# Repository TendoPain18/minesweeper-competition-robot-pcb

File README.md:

# Minesweeper Competition Robot — PCB Design 🤖💣

Custom KiCad-designed PCBs for a minesweeper competition robot, consisting of a **Control PCB** housing the main microcontroller and sensing/driving circuitry, and a **Power PCB** acting as a smart relay system for safely switching robot subsystems on and off.

<div align="center">
  
</div>

<br>
<div align="center">
  
</div>

## 📋 About

Both PCBs were fully designed from schematic to layout in **KiCad** and manufactured as real printed circuit boards. The two boards work together: the Control PCB handles all logic, motor driving, sensing, and protection, while the Power PCB receives switching commands from the Control PCB and safely controls power delivery to the robot's subsystems.

## 🛠️ Tools Used

- **KiCad** — Schematic capture and PCB layout
- **Arduino IDE** — Firmware for the Arduino Mega

---

## 🟦 Control PCB

The brain of the robot. Hosts the microcontroller and all peripheral circuitry needed to drive motors, read sensors, and manage safe shutdown.

<div align="center">
  
</div>

<div align="center">
  
</div>

### Key Components

- **Arduino Mega** — Main microcontroller
- **Two HW-315 Motor Driver Modules** — Drive the main locomotion motors
- **H-Bridge** — Additional motor driving stage
- **Two MPU-6050 IMUs** — Inertial measurement units for orientation sensing
- **Auto Safe-Shutdown Circuit** — Capacitor-backed circuit using ICs, capacitors, and resistors that detects power loss and safely closes the system before supply rails collapse

### Connector Pins / Interfaces

| Interface | Description |
|-----------|-------------|
| Motor Control ×2 | PWM/direction signals for drive motors |
| Motor Driver ×2 | Power outputs to HW-315 modules |
| Encoder ×2 | Quadrature encoder inputs for wheel odometry |
| Arm Motor | Control signal for the mine-detection arm |
| 9V Battery | Main power input |
| Power PCB Link | Control signals sent to the Power PCB |

### PCB Photos

<div align="center">
  
</div>

<div align="center">

</div>

### Safe Shutdown Circuit

A key protection feature of the Control PCB is the automatic safe-shutdown circuit. When the power supply is cut or drops below a safe threshold, the capacitor bank holds enough energy to allow the ICs to complete a controlled shutdown sequence, preventing state corruption and protecting the motor drivers from abrupt power loss.

---

## 🟥 Power PCB

Acts as a smart relay board, receiving switching signals from the Control PCB and toggling power to the robot's subsystems in a safe, controlled manner.

<div align="center">
  
</div>

<div align="center">
  
</div>

### Key Features

- Receives control signals from the Control PCB
- Safely switches power to robot subsystems on and off
- Protects against back-EMF and switching transients
- Designed for low-resistance power paths to minimise losses

### PCB Photos

<div align="center">
  
</div>

<div align="center">

</div>

---

## 🖨️ Manufactured Boards

<div align="center">
  
</div>

*Fully assembled and populated PCBs ready for robot integration*

---

## 📄 License

This project is licensed under the MIT License - see the [LICENSE](LICENSE) file for details.

## 🙏 Acknowledgments

- KiCad open-source EDA tool
- Competition organizers for the design challenge

## <!-- CONTACT -->
<div id="toc" align="center">
  <ul style="list-style: none">
    <summary>
      <h2 align="center">
        🚀
        CONTACT ME
        🚀
      </h2>
    </summary>
  </ul>
</div>
<table align="center" style="width: 100%; max-width: 600px;">
<tr>
  <td style="width: 20%; text-align: center;">
    
  </td>
  <td style="width: 20%; text-align: center;">
    
  </td>
  <td style="width: 20%; text-align: center;">
    
  </td>
  <td style="width: 20%; text-align: center;">
    
  </td>
  <td style="width: 20%; text-align: center;">
    
  </td>
</tr>
</table>
<!-- END CONTACT -->

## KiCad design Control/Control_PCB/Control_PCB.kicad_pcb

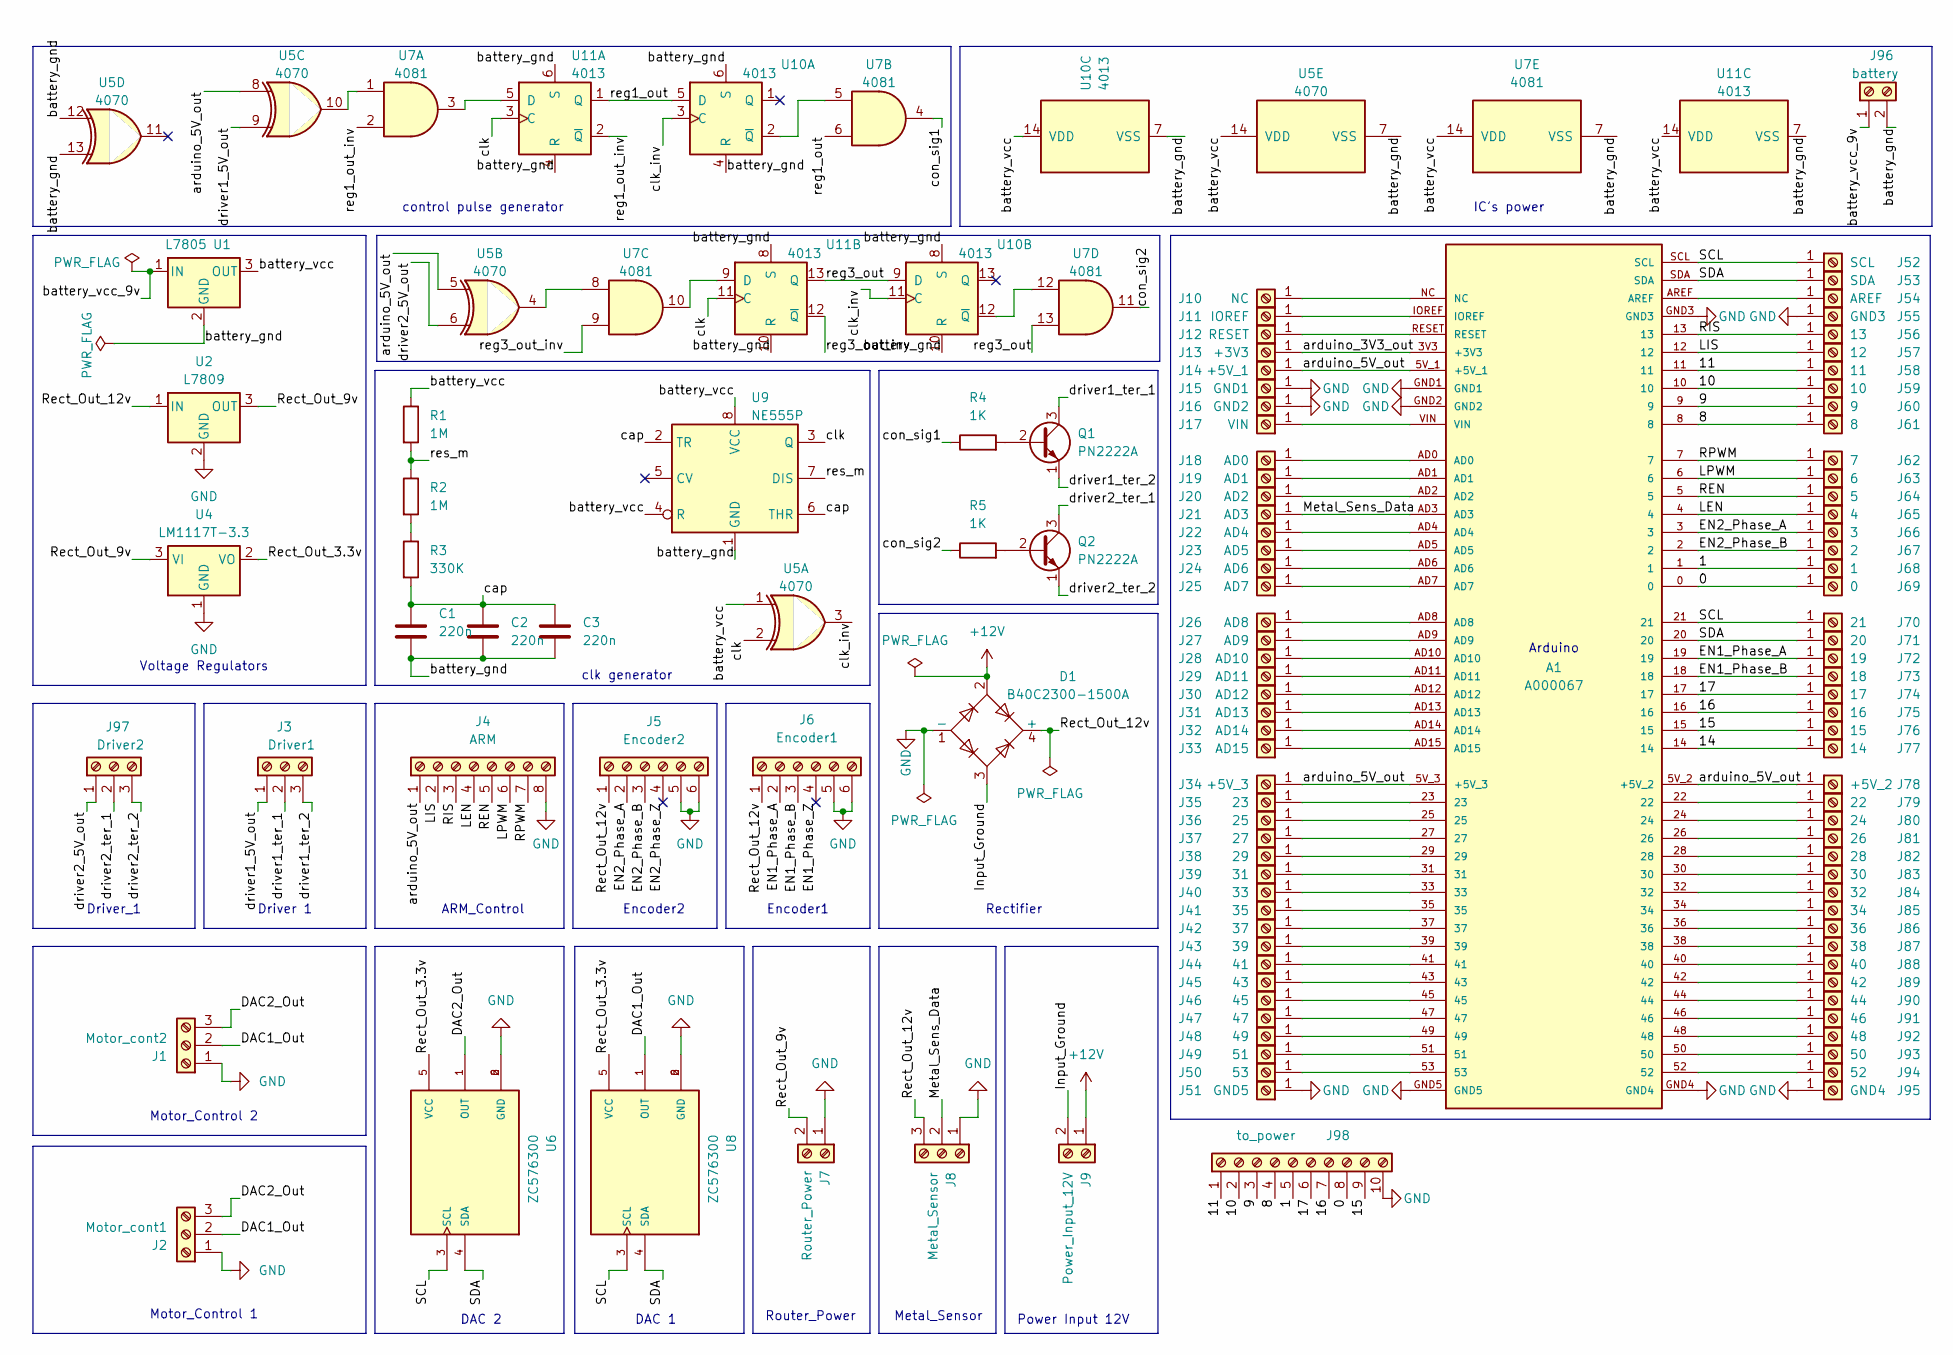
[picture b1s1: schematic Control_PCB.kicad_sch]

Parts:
A1: A000067; Arduino_Mega
C1, C2, C3: 220n; C_Disc_D7.5mm_W5.0mm_P7.50mm
D1: B40C2300-1500A; Diode_Bridge_19.0x3.5x10.0mm_P5.0mm
J1: Motor_cont2; JST_XH_B3B-XH-A_1x03_P2.50mm_Vertical
J2: Motor_cont1; JST_XH_B3B-XH-A_1x03_P2.50mm_Vertical
J3: Driver1; JST_XH_B3B-XH-A_1x03_P2.50mm_Vertical
J4: ARM; JST_XH_B8B-XH-A_1x08_P2.50mm_Vertical
J5: Encoder2; JST_XH_B6B-XH-A_1x06_P2.50mm_Vertical
J6: Encoder1; JST_XH_B6B-XH-A_1x06_P2.50mm_Vertical
J7: Router_Power; TerminalBlock_bornier-2_P5.08mm
J8: Metal_Sensor; TerminalBlock_bornier-3_P5.08mm
J9: Power_Input_12V; TerminalBlock_bornier-2_P5.08mm
J10: NC; Pin_Hole_0.9
J11: IOREF; Pin_Hole_0.9
J12: RESET; Pin_Hole_0.9
J13: +3V3; Pin_Hole_0.9
J14: +5V_1; Pin_Hole_0.9
J15: GND1; Pin_Hole_0.9
J16: GND2; Pin_Hole_0.9
J17: VIN; Pin_Hole_0.9
J18: AD0; Pin_Hole_0.9
J19: AD1; Pin_Hole_0.9
J20: AD2; Pin_Hole_0.9
J21: AD3; Pin_Hole_0.9
J22: AD4; Pin_Hole_0.9
J23: AD5; Pin_Hole_0.9
J24: AD6; Pin_Hole_0.9
J25: AD7; Pin_Hole_0.9
J26: AD8; Pin_Hole_0.9
J27: AD9; Pin_Hole_0.9
J28: AD10; Pin_Hole_0.9
J29: AD11; Pin_Hole_0.9
J30: AD12; Pin_Hole_0.9
J31: AD13; Pin_Hole_0.9
J32: AD14; Pin_Hole_0.9
J33: AD15; Pin_Hole_0.9
J34: +5V_3; Pin_Hole_0.9
J35: 23; Pin_Hole_0.9
J36: 25; Pin_Hole_0.9
J37: 27; Pin_Hole_0.9
J38: 29; Pin_Hole_0.9
J39: 31; Pin_Hole_0.9
J40: 33; Pin_Hole_0.9
J41: 35; Pin_Hole_0.9
J42: 37; Pin_Hole_0.9
J43: 39; Pin_Hole_0.9
J44: 41; Pin_Hole_0.9
J45: 43; Pin_Hole_0.9
J46: 45; Pin_Hole_0.9
J47: 47; Pin_Hole_0.9
J48: 49; Pin_Hole_0.9
J49: 51; Pin_Hole_0.9
J50: 53; Pin_Hole_0.9
J51: GND5; Pin_Hole_0.9
J52: SCL; Pin_Hole_0.9
J53: SDA; Pin_Hole_0.9
J54: AREF; Pin_Hole_0.9
J55: GND3; Pin_Hole_0.9
J56: 13; Pin_Hole_0.9
J57: 12; Pin_Hole_0.9
J58: 11; Pin_Hole_0.9
J59: 10; Pin_Hole_0.9
J60: 9; Pin_Hole_0.9
J61: 8; Pin_Hole_0.9
J62: 7; Pin_Hole_0.9
J63: 6; Pin_Hole_0.9
J64: 5; Pin_Hole_0.9
J65: 4; Pin_Hole_0.9
J66: 3; Pin_Hole_0.9
J67: 2; Pin_Hole_0.9
J68: 1; Pin_Hole_0.9
J69: 0; Pin_Hole_0.9
J70: 21; Pin_Hole_0.9
J71: 20; Pin_Hole_0.9
J72: 19; Pin_Hole_0.9
J73: 18; Pin_Hole_0.9
J74: 17; Pin_Hole_0.9
J75: 16; Pin_Hole_0.9
J76: 15; Pin_Hole_0.9
J77: 14; Pin_Hole_0.9
J78: +5V_2; Pin_Hole_0.9
J79: 22; Pin_Hole_0.9
J80: 24; Pin_Hole_0.9
J81: 26; Pin_Hole_0.9
J82: 28; Pin_Hole_0.9
J83: 30; Pin_Hole_0.9
J84: 32; Pin_Hole_0.9
J85: 34; Pin_Hole_0.9
J86: 36; Pin_Hole_0.9
J87: 38; Pin_Hole_0.9
J88: 40; Pin_Hole_0.9
J89: 42; Pin_Hole_0.9
J90: 44; Pin_Hole_0.9
J91: 46; Pin_Hole_0.9
J92: 48; Pin_Hole_0.9
J93: 50; Pin_Hole_0.9
J94: 52; Pin_Hole_0.9
J95: GND4; Pin_Hole_0.9
J96: battery; JST_XH_B2B-XH-A_1x02_P2.50mm_Vertical
J97: Driver2; JST_XH_B3B-XH-A_1x03_P2.50mm_Vertical
J98: to_power; JST_XH_B10B-XH-A_1x10_P2.50mm_Vertical
Q1, Q2: PN2222A; TO-92L_Inline_Wide
R1, R2: 1M; R_Axial_DIN0204_L3.6mm_D1.6mm_P7.62mm_Horizontal
R3: 330K; R_Axial_DIN0204_L3.6mm_D1.6mm_P7.62mm_Horizontal
R4, R5: 1K; R_Axial_DIN0204_L3.6mm_D1.6mm_P7.62mm_Horizontal
U1: L7805; TO-220-3_Vertical
U2: L7809; TO-220-3_Vertical
U4: LM1117T-3.3; TO-220-3_Vertical
U5: 4070; DIP-14_W7.62mm_LongPads
U6, U8: ZC576300; MODULE_ZC576300; PARTREV v14
U7: 4081; DIP-14_W7.62mm_LongPads
U9: NE555P; DIP-8_W7.62mm
U10, U11: 4013; DIP-14_W7.62mm_LongPads

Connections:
+12V: D1.2, J9.1
/0: A1.0, J69.1, J98.8
/1: A1.1, J68.1, J98.5
/8: A1.8, J61.1, J98.4
/9: A1.9, J60.1, J98.3
/10: A1.10, J59.1, J98.2
/11: A1.11, J58.1, J98.1
/14: A1.14, J77.1
/15: A1.15, J76.1, J98.9
/16: A1.16, J75.1, J98.7
/17: A1.17, J74.1, J98.6
/DAC1_Out: J1.2, J2.2, U8.1 (OUT)
/DAC2_Out: J1.3, J2.3, U6.1 (OUT)
/EN1_Phase_A: A1.19, J6.2, J72.1
/EN1_Phase_B: A1.18, J6.3, J73.1
/EN1_Phase_Z: J6.4
/EN2_Phase_A: A1.3, J5.2, J66.1
/EN2_Phase_B: A1.2, J5.3, J67.1
/EN2_Phase_Z: J5.4
/Input_Ground: D1.3, J9.2
/LEN: A1.4, J4.4, J65.1
/LIS: A1.12, J4.2, J57.1
/LPWM: A1.6, J4.6, J63.1
/Metal_Sens_Data: A1.AD3, J8.2, J21.1
/REN: A1.5, J4.5, J64.1
/RIS: A1.13, J4.3, J56.1
/RPWM: A1.7, J4.7, J62.1
/Rect_Out_3.3v: U4.2 (VO), U6.5 (VCC), U8.5 (VCC)
/Rect_Out_9v: J7.2, U2.3 (OUT), U4.3 (VI)
/Rect_Out_12v: D1.4 (+), J5.1, J6.1, J8.3, U2.1 (IN)
/SCL: A1.21, A1.SCL, J52.1, J70.1, U6.3 (SCL), U8.3 (SCL)
/SDA: A1.20, A1.SDA, J53.1, J71.1, U6.4 (SDA), U8.4 (SDA)
/arduino_3V3_out: A1.3V3 (+3V3), J13.1
/arduino_5V_out: A1.5V_1 (+5V_1), A1.5V_2 (+5V_2), A1.5V_3 (+5V_3), J4.1, J14.1, J34.1, J78.1, U5.5, U5.8
/battery_gnd: C1.2, C2.2, C3.2, J96.2, U1.2 (GND), U5.7 (VSS), U5.12, U5.13, U7.7 (VSS), U9.1 (GND), U10.4 (R), U10.6 (S), U10.7 (VSS), U10.8 (S), U10.10 (R), U11.4 (R), U11.6 (S), U11.7 (VSS), U11.8 (S), U11.10 (R)
/battery_vcc: R1.1, U1.3 (OUT), U5.1, U5.14 (VDD), U7.14 (VDD), U9.4 (R), U9.8 (VCC), U10.14 (VDD), U11.14 (VDD)
/battery_vcc_9v: J96.1, U1.1 (IN)
/cap: C1.1, C2.1, C3.1, R3.2, U9.2 (TR), U9.6 (THR)
/clk: U5.2, U9.3 (Q), U11.3 (C), U11.11 (C)
/clk_inv: U5.3, U10.3 (C), U10.11 (C)
/con_sig1: R4.1, U7.4
/con_sig2: R5.1, U7.11
/driver1_5V_out: J3.1, U5.9
/driver1_ter_1: J3.2, Q1.3 (C)
/driver1_ter_2: J3.3, Q1.1 (E)
/driver2_5V_out: J97.1, U5.6
/driver2_ter_1: J97.2, Q2.3 (C)
/driver2_ter_2: J97.3, Q2.1 (E)
/reg1_out: U7.6, U10.5 (D), U11.1 (Q)
/reg1_out_inv: U7.2, U11.2 (~Q)
/reg3_out: U7.13, U10.9 (D), U11.13 (Q)
/reg3_out_inv: U7.9, U11.12 (~Q)
/res_m: R1.2, R2.1, U9.7 (DIS)
GND: A1.GND1, A1.GND2, A1.GND3, A1.GND4, A1.GND5, D1.1 (-), J1.1, J2.1, J4.8, J5.5, J5.6, J6.5, J6.6, J7.1, J8.1, J15.1, J16.1, J51.1, J55.1, J95.1, J98.10, U2.2 (GND), U4.1 (GND), U6.2 (GND), U6.6 (GND), U8.2 (GND), U8.6 (GND)
unnamed: A1.NC, J10.1
unnamed: A1.IOREF, J11.1
unnamed: A1.RESET, J12.1
unnamed: A1.VIN, J17.1
unnamed: A1.AD0, J18.1
unnamed: A1.AD1, J19.1
unnamed: A1.AD2, J20.1
unnamed: A1.AD4, J22.1
unnamed: A1.AD5, J23.1
unnamed: A1.AD6, J24.1
unnamed: A1.AD7, J25.1
unnamed: A1.AD8, J26.1
unnamed: A1.AD9, J27.1
unnamed: A1.AD10, J28.1
unnamed: A1.AD11, J29.1
unnamed: A1.AD12, J30.1
unnamed: A1.AD13, J31.1
unnamed: A1.AD14, J32.1
unnamed: A1.AD15, J33.1
unnamed: A1.23, J35.1
unnamed: A1.25, J36.1
unnamed: A1.27, J37.1
unnamed: A1.29, J38.1
unnamed: A1.31, J39.1
unnamed: A1.33, J40.1
unnamed: A1.35, J41.1
unnamed: A1.37, J42.1
unnamed: A1.39, J43.1
unnamed: A1.41, J44.1
unnamed: A1.43, J45.1
unnamed: A1.45, J46.1
unnamed: A1.47, J47.1
unnamed: A1.49, J48.1
unnamed: A1.51, J49.1
unnamed: A1.53, J50.1
unnamed: A1.AREF, J54.1
unnamed: A1.22, J79.1
unnamed: A1.24, J80.1
unnamed: A1.26, J81.1
unnamed: A1.28, J82.1
unnamed: A1.30, J83.1
unnamed: A1.32, J84.1
unnamed: A1.34, J85.1
unnamed: A1.36, J86.1
unnamed: A1.38, J87.1
unnamed: A1.40, J88.1
unnamed: A1.42, J89.1
unnamed: A1.44, J90.1
unnamed: A1.46, J91.1
unnamed: A1.48, J92.1
unnamed: A1.50, J93.1
unnamed: A1.52, J94.1
unnamed: Q1.2 (B), R4.2
unnamed: Q2.2 (B), R5.2
unnamed: R2.2, R3.1
unnamed: U5.4, U7.8
unnamed: U5.10, U7.1
unnamed: U7.5, U10.2 (~Q)
unnamed: U7.12, U10.12 (~Q)
unnamed: U7.3, U11.5 (D)
unnamed: U7.10, U11.9 (D)

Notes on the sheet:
Driver_1
clk generator
Voltage Regulators
Power Input 12V
Router_Power
ARM_Control
DAC 1
IC's power
Rectifier
Encoder2
Motor_Control 1
Arduino
Encoder1
Metal_Sensor
Motor_Control 2
DAC 2
control pulse generator
Driver 1

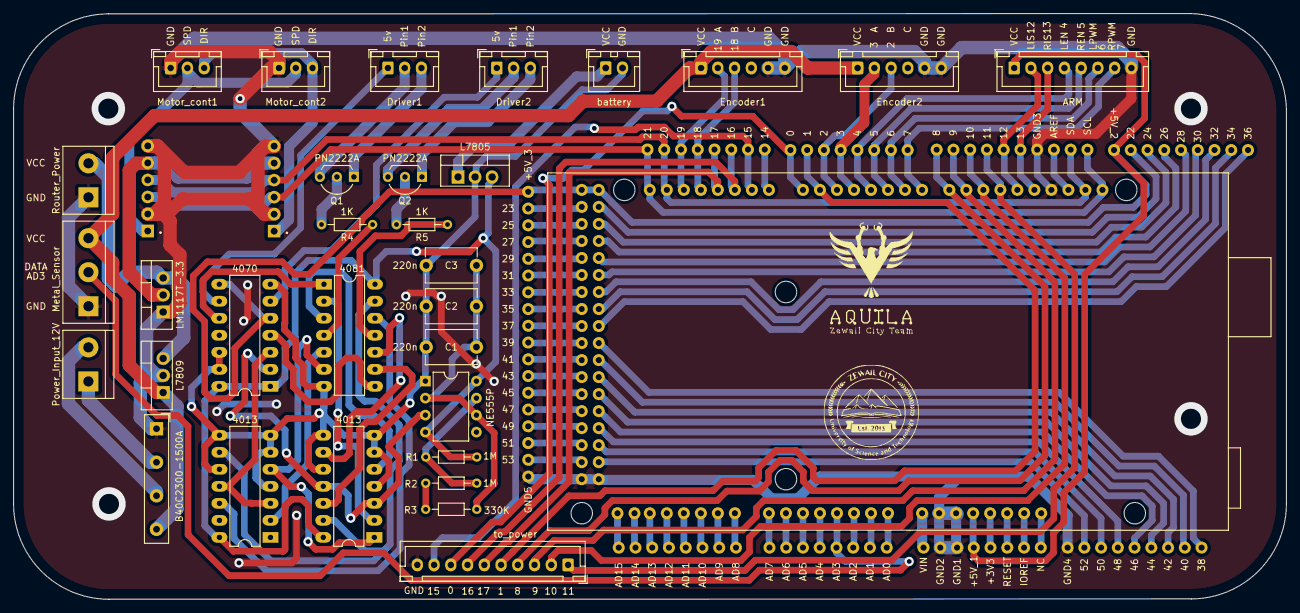
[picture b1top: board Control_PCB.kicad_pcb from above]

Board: 2 copper layers, 190.0 x 87.4 mm, 120 parts (0 on the bottom side), 113 nets.

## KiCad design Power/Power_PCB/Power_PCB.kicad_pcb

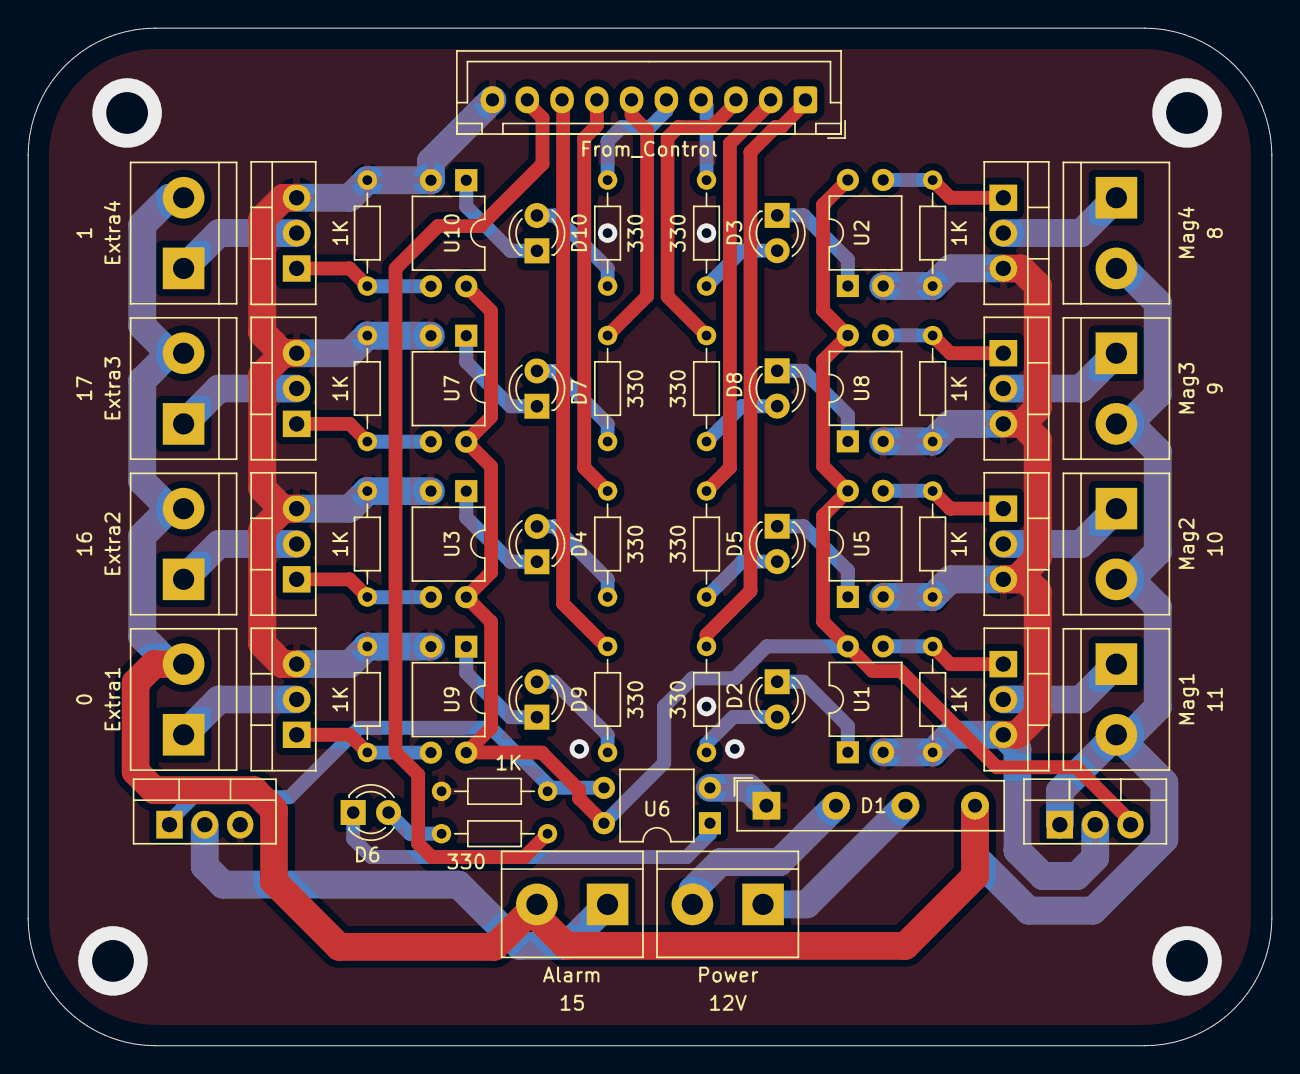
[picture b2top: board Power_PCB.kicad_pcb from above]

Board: 2 copper layers, 89.4 x 73.2 mm, 58 parts (0 on the bottom side), 50 nets.

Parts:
1K, 1K#2, 1K#3, 1K#4, 1K#5, 1K#6, 1K#7, 1K#8, 1K#9: 1K; R_Axial_DIN0204_L3.6mm_D1.6mm_P7.62mm_Horizontal
330, 330#2, 330#3, 330#4, 330#5, 330#6, 330#7, 330#8, 330#9: 330; R_Axial_DIN0204_L3.6mm_D1.6mm_P7.62mm_Horizontal
Alarm: Alarm; TerminalBlock_bornier-2_P5.08mm
D1: B40C2300-1500A; Diode_Bridge_19.0x3.5x10.0mm_P5.0mm
D2, D3, D4, D5, D6, D7, D8, D9, D10: LED; LED_D3.0mm
Extra1: Extra1; TerminalBlock_bornier-2_P5.08mm
Extra2: Extra2; TerminalBlock_bornier-2_P5.08mm
Extra3: Extra3; TerminalBlock_bornier-2_P5.08mm
Extra4: Extra4; TerminalBlock_bornier-2_P5.08mm
From_Control: from_control; JST_XH_B10B-XH-A_1x10_P2.50mm_Vertical
Mag1: Mag1; TerminalBlock_bornier-2_P5.08mm
Mag2: Mag2; TerminalBlock_bornier-2_P5.08mm
Mag3: Mag3; TerminalBlock_bornier-2_P5.08mm
Mag4: Mag4; TerminalBlock_bornier-2_P5.08mm
Power: main_power; TerminalBlock_bornier-2_P5.08mm
Q1, Q2, Q3, Q4, Q5, Q6, Q7, Q8, Q9: IRF9540N; TO-220-3_Vertical
U1, U2, U3, U5, U6, U7, U8, U9, U10: EL817; DIP-4_W7.62mm
U4: L7805; TO-220-3_Vertical

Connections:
/0: 330#6.1, From_Control.8
/1: 330#7.1, From_Control.5
/8: 330.1, From_Control.4
/9: 330#8.1, From_Control.3
/10: 330#4.1, From_Control.2
/11: 330#3.1, From_Control.1
/15: 330#5.1, From_Control.9
/16: 330#2.1, From_Control.7
/17: 330#9.1, From_Control.6
/Pwr1: D1.2, Power.2
/Pwr1_Gnd: D1.3, Power.1
/Rect_Out_5v: U1.4, U2.4, U3.4, U4.3 (OUT), U5.4, U6.4, U7.4, U8.4, U9.4, U10.4
/Rect_Out_12v: Alarm.2, D1.4 (+), Extra1.2, Extra2.2, Extra3.2, Extra4.2, Mag1.2, Mag2.2, Mag3.2, Mag4.2, U4.1 (IN)
/alarm_gnd: Alarm.1, Q5.2 (D)
/extra1_gnd: Extra1.1, Q8.2 (D)
/extra2_gnd: Extra2.1, Q3.2 (D)
/extra3_gnd: Extra3.1, Q6.2 (D)
/extra4_gnd: Extra4.1, Q9.2 (D)
/mag1_gnd: Mag1.1, Q1.2 (D)
/mag2_gnd: Mag2.1, Q4.2 (D)
/mag3_gnd: Mag3.1, Q7.2 (D)
/mag4_gnd: Mag4.1, Q2.2 (D)
GND: 1K.2, 1K#2.2, 1K#3.2, 1K#4.2, 1K#5.2, 1K#6.2, 1K#7.2, 1K#8.2, 1K#9.2, D1.1 (-), From_Control.10, Q1.3 (S), Q2.3 (S), Q3.3 (S), Q4.3 (S), Q5.3 (S), Q6.3 (S), Q7.3 (S), Q8.3 (S), Q9.3 (S), U1.2, U2.2, U3.2, U4.2 (GND), U5.2, U6.2, U7.2, U8.2, U9.2, U10.2
unnamed: 330#3.2, D2.2 (A)
unnamed: D2.1 (K), U1.1
unnamed: 330.2, D3.2 (A)
unnamed: D3.1 (K), U2.1
unnamed: 330#2.2, D4.2 (A)
unnamed: D4.1 (K), U3.1
unnamed: 330#4.2, D5.2 (A)
unnamed: D5.1 (K), U5.1
unnamed: 330#5.2, D6.2 (A)
unnamed: D6.1 (K), U6.1
unnamed: 330#9.2, D7.2 (A)
unnamed: D7.1 (K), U7.1
unnamed: 330#8.2, D8.2 (A)
unnamed: D8.1 (K), U8.1
unnamed: 330#6.2, D9.2 (A)
unnamed: D9.1 (K), U9.1
unnamed: 330#7.2, D10.2 (A)
unnamed: D10.1 (K), U10.1
unnamed: 1K#3.1, Q1.1 (G), U1.3
unnamed: 1K#4.1, Q2.1 (G), U2.3
unnamed: 1K#2.1, Q3.1 (G), U3.3
unnamed: 1K#6.1, Q4.1 (G), U5.3
unnamed: 1K#8.1, Q5.1 (G), U6.3
unnamed: 1K.1, Q6.1 (G), U7.3
unnamed: 1K#5.1, Q7.1 (G), U8.3
unnamed: 1K#9.1, Q8.1 (G), U9.3
unnamed: 1K#7.1, Q9.1 (G), U10.3

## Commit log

2026-04-20 Upload Files
2026-04-22 chore: Auto-sync contact section from profile
